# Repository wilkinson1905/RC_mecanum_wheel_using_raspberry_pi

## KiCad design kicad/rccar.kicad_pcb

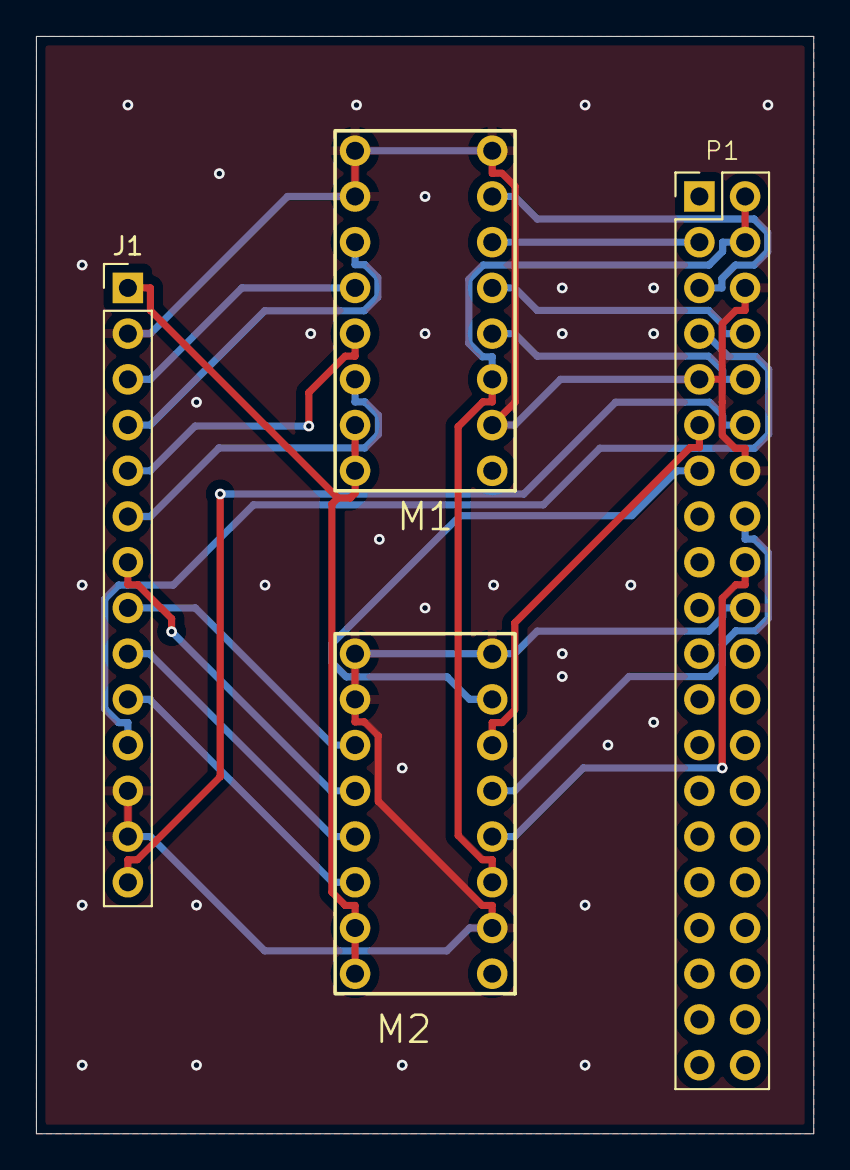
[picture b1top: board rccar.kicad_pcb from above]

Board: 2 copper layers, 43.2 x 61.0 mm, 4 parts (0 on the bottom side), 21 nets.

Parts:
J1: Conn_01x14_Pin; PinHeader_1x14_P2.54mm_Vertical
M1, M2: TC78H653FTG
P1: Raspberry_Pi_4_GPIO; Raspberry_Pi_4

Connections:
+5V: M1.3 (STDY), M2.3 (STDY), P1.2 (5V), P1.4 (5V)
+6V: J1.1, M1.15 (VM), M1.16 (VM), M2.15 (VM), M2.16 (VM)
FRONT_LEFT_MOTOR+: J1.3, M1.12 (OUT1)
FRONT_LEFT_MOTOR-: J1.4, M1.11 (OUT2)
FRONT_RIGHT_MOTOR+: J1.5, M1.13 (OUT3)
FRONT_RIGHT_MOTOR-: J1.6, M1.14 (OUT4)
GND: J1.2, J1.12, J1.13, M1.2 (MODE), M1.8 (GND), M1.9 (GND), M1.10 (GND), M2.2 (MODE), M2.8 (GND), M2.9 (GND), M2.10 (GND), P1.6 (GND), P1.9 (GND), P1.14 (GND), P1.20 (GND)
LED_SIGNAL1: J1.11, P1.7 (GPIO4)
LED_SIGNAL2: J1.14, P1.12 (GPIO18)
MOTOR_SIGNAL1-1: M1.6 (IN1), P1.3 (GPIO2)
MOTOR_SIGNAL1-2: M1.7 (IN2), P1.5 (GPIO3)
MOTOR_SIGNAL2-1: M1.5 (IN3), P1.8 (GPIO14)
MOTOR_SIGNAL2-2: M1.4 (IN4), P1.10 (GPIO15)
MOTOR_SIGNAL3-1: M2.6 (IN1), P1.11 (GPIO27)
MOTOR_SIGNAL3-2: M2.7 (IN2), P1.13 (GPIO17)
MOTOR_SIGNAL4-1: M2.5 (IN3), P1.16 (GPIO23)
MOTOR_SIGNAL4-2: M2.4 (IN4), P1.18 (GPIO24)
REAR_LEFT_MOTOR+: J1.7, M2.12 (OUT1)
REAR_LEFT_MOTOR-: J1.8, M2.11 (OUT2)
REAR_RIGHT_MOTOR+: J1.9, M2.13 (OUT3)
REAR_RIGHT_MOTOR-: J1.10, M2.14 (OUT4)

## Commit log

2024-12-19 add kicad data
2024-12-19 回路図を追加
2024-12-19 回路図の名前を修正
2024-12-19 Rename cirkit.pdf to circuit.pdf
2024-12-19 add circuit jpg
